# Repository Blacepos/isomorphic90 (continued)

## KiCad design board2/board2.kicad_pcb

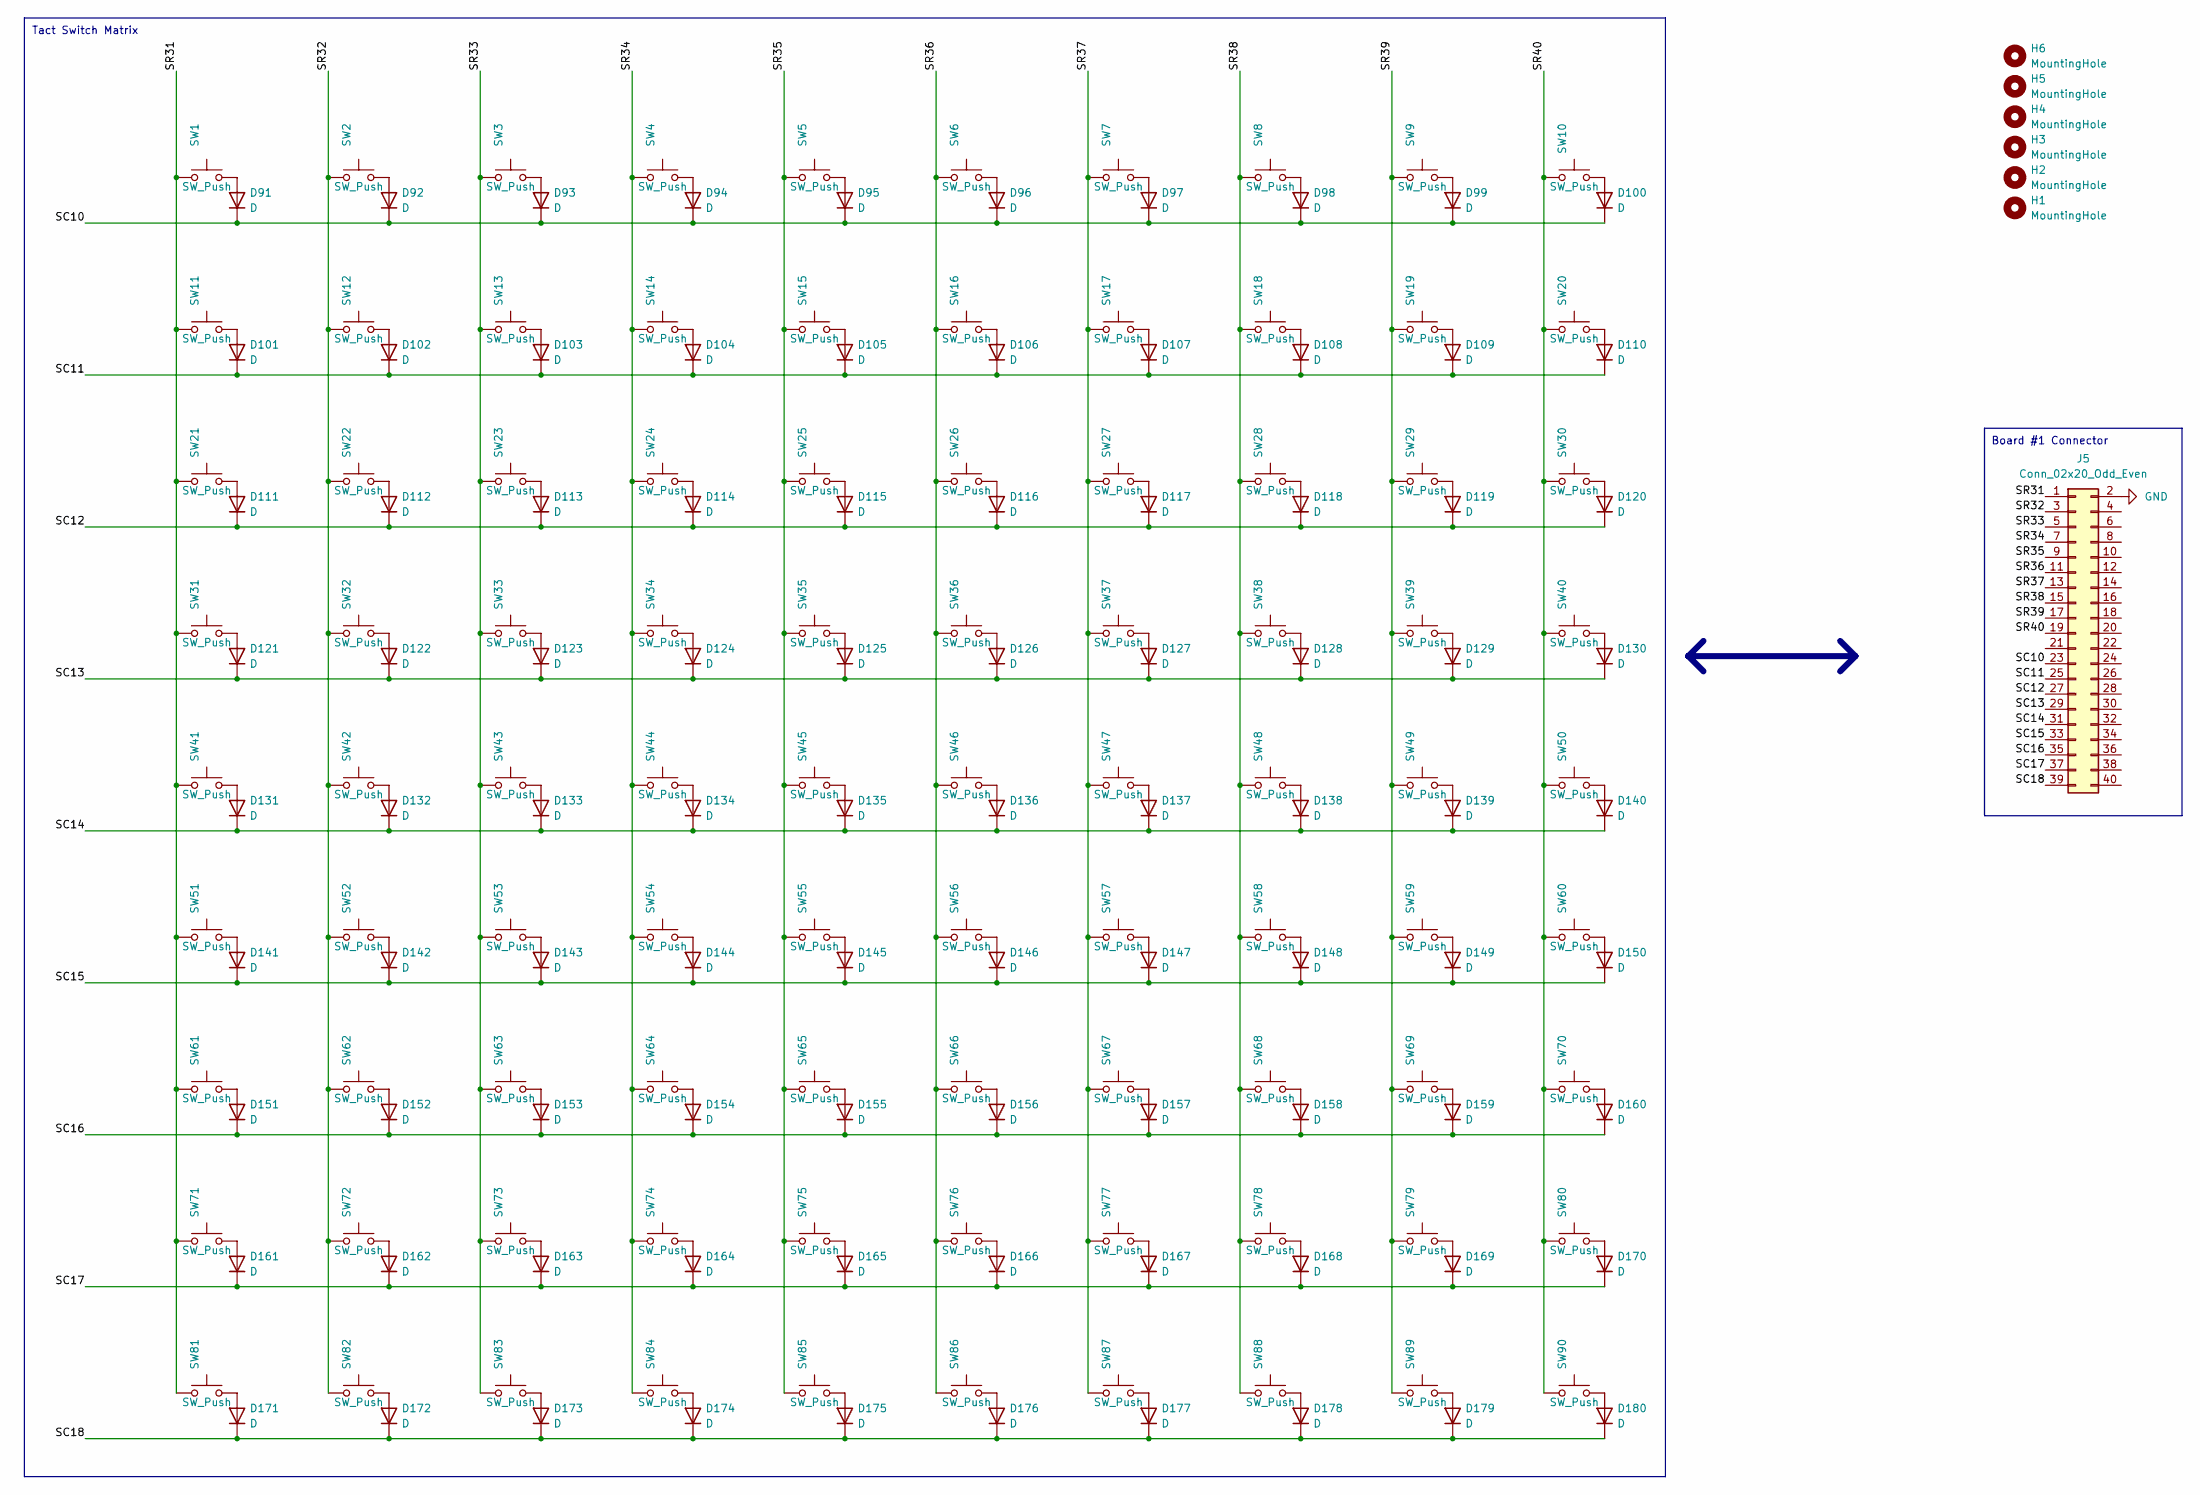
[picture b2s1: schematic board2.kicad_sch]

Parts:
D91, D92, D93, D94, D95, D96, D97, D98, D99, D100, D101, D102, D103, D104, D105, D106, D107, D108, D109, D110, D111, D112, D113, D114, D115, D116, D117, D118, D119, D120, D121, D122, D123, D124, D125, D126, D127, D128, D129, D130, D131, D132, D133, D134, D135, D136, D137, D138, D139, D140, D141, D142, D143, D144, D145, D146, D147, D148, D149, D150, D151, D152, D153, D154, D155, D156, D157, D158, D159, D160, D161, D162, D163, D164, D165, D166, D167, D168, D169, D170, D171, D172, D173, D174, D175, D176, D177, D178, D179, D180: D; D_SOD-123
H1, H2, H3, H4, H5, H6: MountingHole; MountingHole_2.2mm_M2
J5: Conn_02x20_Odd_Even; IDC-Header_2x20_P2.54mm_Vertical
SW1, SW2, SW3, SW4, SW5, SW6, SW7, SW8, SW9, SW10, SW11, SW12, SW13, SW14, SW15, SW16, SW17, SW18, SW19, SW20, SW21, SW22, SW23, SW24, SW25, SW26, SW27, SW28, SW29, SW30, SW31, SW32, SW33, SW34, SW35, SW36, SW37, SW38, SW39, SW40, SW41, SW42, SW43, SW44, SW45, SW46, SW47, SW48, SW49, SW50, SW51, SW52, SW53, SW54, SW55, SW56, SW57, SW58, SW59, SW60, SW61, SW62, SW63, SW64, SW65, SW66, SW67, SW68, SW69, SW70, SW71, SW72, SW73, SW74, SW75, SW76, SW77, SW78, SW79, SW80, SW81, SW82, SW83, SW84, SW85, SW86, SW87, SW88, SW89, SW90: SW_Push; SW_PUSH_6mm_H5mm

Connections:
/SC10: D91.1 (K), D92.1 (K), D93.1 (K), D94.1 (K), D95.1 (K), D96.1 (K), D97.1 (K), D98.1 (K), D99.1 (K), D100.1 (K), J5.23
/SC11: D101.1 (K), D102.1 (K), D103.1 (K), D104.1 (K), D105.1 (K), D106.1 (K), D107.1 (K), D108.1 (K), D109.1 (K), D110.1 (K), J5.25
/SC12: D111.1 (K), D112.1 (K), D113.1 (K), D114.1 (K), D115.1 (K), D116.1 (K), D117.1 (K), D118.1 (K), D119.1 (K), D120.1 (K), J5.27
/SC13: D121.1 (K), D122.1 (K), D123.1 (K), D124.1 (K), D125.1 (K), D126.1 (K), D127.1 (K), D128.1 (K), D129.1 (K), D130.1 (K), J5.29
/SC14: D131.1 (K), D132.1 (K), D133.1 (K), D134.1 (K), D135.1 (K), D136.1 (K), D137.1 (K), D138.1 (K), D139.1 (K), D140.1 (K), J5.31
/SC15: D141.1 (K), D142.1 (K), D143.1 (K), D144.1 (K), D145.1 (K), D146.1 (K), D147.1 (K), D148.1 (K), D149.1 (K), D150.1 (K), J5.33
/SC16: D151.1 (K), D152.1 (K), D153.1 (K), D154.1 (K), D155.1 (K), D156.1 (K), D157.1 (K), D158.1 (K), D159.1 (K), D160.1 (K), J5.35
/SC17: D161.1 (K), D162.1 (K), D163.1 (K), D164.1 (K), D165.1 (K), D166.1 (K), D167.1 (K), D168.1 (K), D169.1 (K), D170.1 (K), J5.37
/SC18: D171.1 (K), D172.1 (K), D173.1 (K), D174.1 (K), D175.1 (K), D176.1 (K), D177.1 (K), D178.1 (K), D179.1 (K), D180.1 (K), J5.39
/SR31: J5.1, SW1.1, SW11.1, SW21.1, SW31.1, SW41.1, SW51.1, SW61.1, SW71.1, SW81.1
/SR32: J5.3, SW2.1, SW12.1, SW22.1, SW32.1, SW42.1, SW52.1, SW62.1, SW72.1, SW82.1
/SR33: J5.5, SW3.1, SW13.1, SW23.1, SW33.1, SW43.1, SW53.1, SW63.1, SW73.1, SW83.1
/SR34: J5.7, SW4.1, SW14.1, SW24.1, SW34.1, SW44.1, SW54.1, SW64.1, SW74.1, SW84.1
/SR35: J5.9, SW5.1, SW15.1, SW25.1, SW35.1, SW45.1, SW55.1, SW65.1, SW75.1, SW85.1
/SR36: J5.11, SW6.1, SW16.1, SW26.1, SW36.1, SW46.1, SW56.1, SW66.1, SW76.1, SW86.1
/SR37: J5.13, SW7.1, SW17.1, SW27.1, SW37.1, SW47.1, SW57.1, SW67.1, SW77.1, SW87.1
/SR38: J5.15, SW8.1, SW18.1, SW28.1, SW38.1, SW48.1, SW58.1, SW68.1, SW78.1, SW88.1
/SR39: J5.17, SW9.1, SW19.1, SW29.1, SW39.1, SW49.1, SW59.1, SW69.1, SW79.1, SW89.1
/SR40: J5.19, SW10.1, SW20.1, SW30.1, SW40.1, SW50.1, SW60.1, SW70.1, SW80.1, SW90.1
GND: J5.2
unnamed: D91.2 (A), SW1.2
unnamed: D92.2 (A), SW2.2
unnamed: D93.2 (A), SW3.2
unnamed: D94.2 (A), SW4.2
unnamed: D95.2 (A), SW5.2
unnamed: D96.2 (A), SW6.2
unnamed: D97.2 (A), SW7.2
unnamed: D98.2 (A), SW8.2
unnamed: D99.2 (A), SW9.2
unnamed: D100.2 (A), SW10.2
unnamed: D101.2 (A), SW11.2
unnamed: D102.2 (A), SW12.2
unnamed: D103.2 (A), SW13.2
unnamed: D104.2 (A), SW14.2
unnamed: D105.2 (A), SW15.2
unnamed: D106.2 (A), SW16.2
unnamed: D107.2 (A), SW17.2
unnamed: D108.2 (A), SW18.2
unnamed: D109.2 (A), SW19.2
unnamed: D110.2 (A), SW20.2
unnamed: D111.2 (A), SW21.2
unnamed: D112.2 (A), SW22.2
unnamed: D113.2 (A), SW23.2
unnamed: D114.2 (A), SW24.2
unnamed: D115.2 (A), SW25.2
unnamed: D116.2 (A), SW26.2
unnamed: D117.2 (A), SW27.2
unnamed: D118.2 (A), SW28.2
unnamed: D119.2 (A), SW29.2
unnamed: D120.2 (A), SW30.2
unnamed: D121.2 (A), SW31.2
unnamed: D122.2 (A), SW32.2
unnamed: D123.2 (A), SW33.2
unnamed: D124.2 (A), SW34.2
unnamed: D125.2 (A), SW35.2
unnamed: D126.2 (A), SW36.2
unnamed: D127.2 (A), SW37.2
unnamed: D128.2 (A), SW38.2
unnamed: D129.2 (A), SW39.2
unnamed: D130.2 (A), SW40.2
unnamed: D131.2 (A), SW41.2
unnamed: D132.2 (A), SW42.2
unnamed: D133.2 (A), SW43.2
unnamed: D134.2 (A), SW44.2
unnamed: D135.2 (A), SW45.2
unnamed: D136.2 (A), SW46.2
unnamed: D137.2 (A), SW47.2
unnamed: D138.2 (A), SW48.2
unnamed: D139.2 (A), SW49.2
unnamed: D140.2 (A), SW50.2
unnamed: D141.2 (A), SW51.2
unnamed: D142.2 (A), SW52.2
unnamed: D143.2 (A), SW53.2
unnamed: D144.2 (A), SW54.2
unnamed: D145.2 (A), SW55.2
unnamed: D146.2 (A), SW56.2
unnamed: D147.2 (A), SW57.2
unnamed: D148.2 (A), SW58.2
unnamed: D149.2 (A), SW59.2
unnamed: D150.2 (A), SW60.2
unnamed: D151.2 (A), SW61.2
unnamed: D152.2 (A), SW62.2
unnamed: D153.2 (A), SW63.2
unnamed: D154.2 (A), SW64.2
unnamed: D155.2 (A), SW65.2
unnamed: D156.2 (A), SW66.2
unnamed: D157.2 (A), SW67.2
unnamed: D158.2 (A), SW68.2
unnamed: D159.2 (A), SW69.2
unnamed: D160.2 (A), SW70.2
unnamed: D161.2 (A), SW71.2
unnamed: D162.2 (A), SW72.2
unnamed: D163.2 (A), SW73.2
unnamed: D164.2 (A), SW74.2
unnamed: D165.2 (A), SW75.2
unnamed: D166.2 (A), SW76.2
unnamed: D167.2 (A), SW77.2
unnamed: D168.2 (A), SW78.2
unnamed: D169.2 (A), SW79.2
unnamed: D170.2 (A), SW80.2
unnamed: D171.2 (A), SW81.2
unnamed: D172.2 (A), SW82.2
unnamed: D173.2 (A), SW83.2
unnamed: D174.2 (A), SW84.2
unnamed: D175.2 (A), SW85.2
unnamed: D176.2 (A), SW86.2
unnamed: D177.2 (A), SW87.2
unnamed: D178.2 (A), SW88.2
unnamed: D179.2 (A), SW89.2
unnamed: D180.2 (A), SW90.2

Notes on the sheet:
Board #1 Connector
Tact Switch Matrix

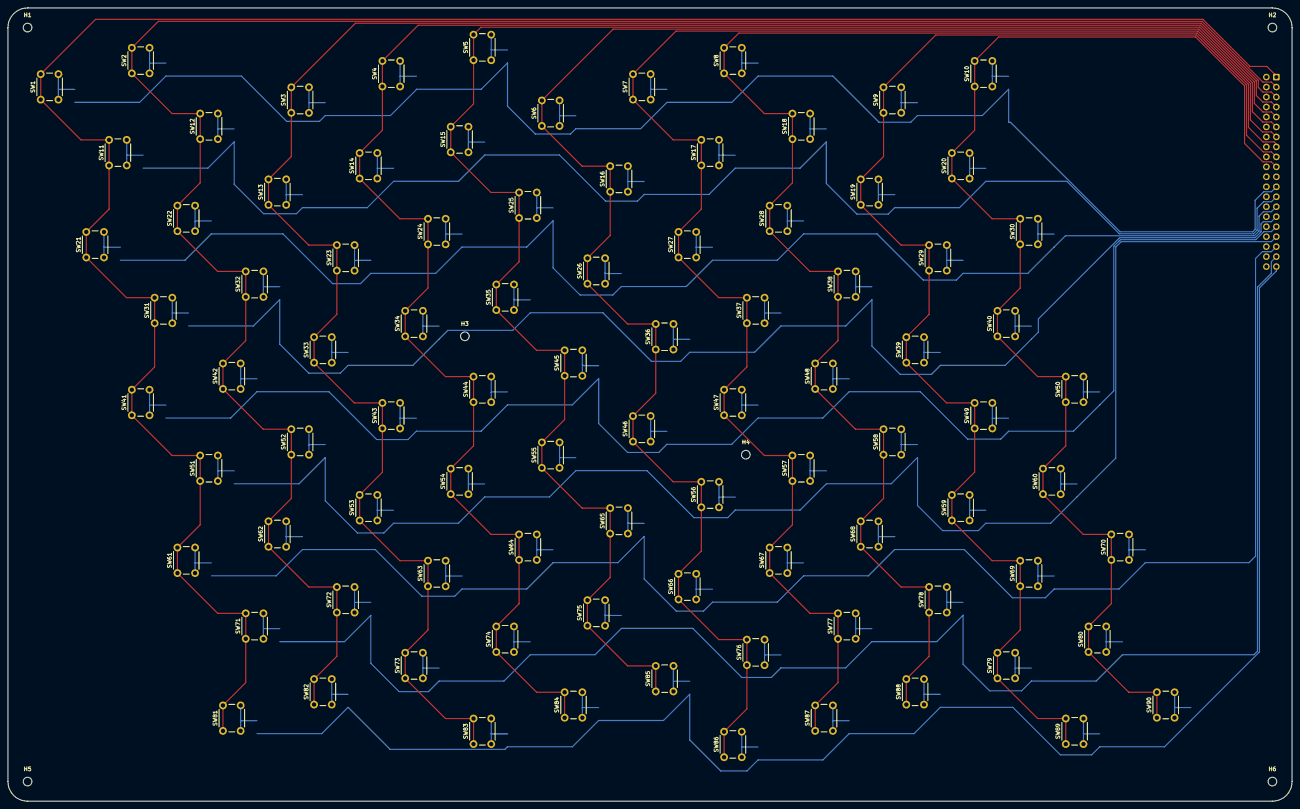
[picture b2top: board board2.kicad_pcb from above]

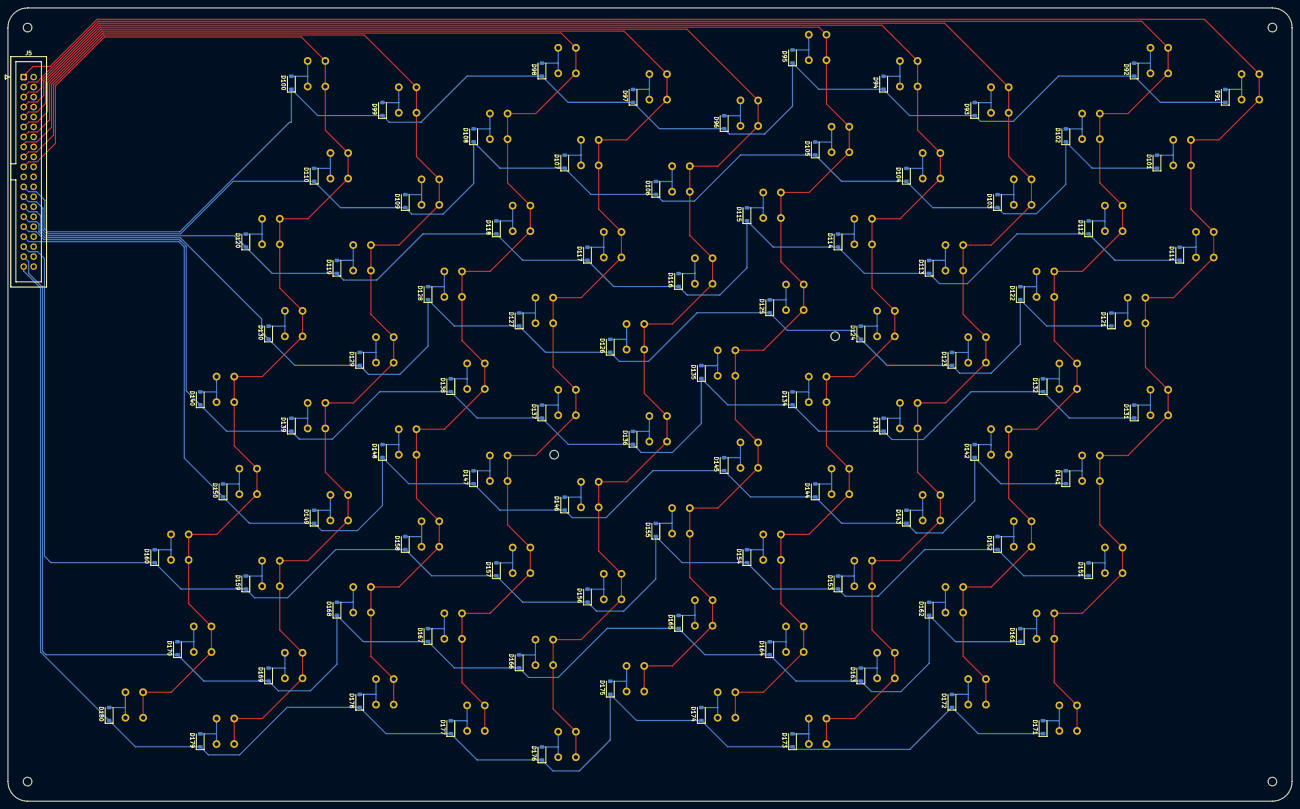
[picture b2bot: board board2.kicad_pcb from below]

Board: 2 copper layers, 327.0 x 202.0 mm, 187 parts (91 on the bottom side), 109 nets.

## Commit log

2025-03-24 Add kicanvas links and fix images
2025-03-24 More accurate statement in README
